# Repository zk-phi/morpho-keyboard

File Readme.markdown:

# Morpho keyboard

スイッチの差し込み位置をずらすことで、一台で色々な Row-staggered 配列を試すことができる分割キーボードです。

スイッチソケットが互い違いに 0.5u 間隔で配置されており、その範囲で好きな位置にキースイッチを移動することができます。

キー数自体も多めになっており、キーマップも含め自分好みのレイアウトを模索することができます。

## 注意

コスト削減のためにプレートの用意がないため、基板のマウント穴とソケットだけでスイッチを支える構造になっています。使い込むうちに、だんだんスイッチの固定がゆるくなってくる可能性が高いです。

打鍵感にこだわった長く使えるキーボード、というよりは自分に合ったキー配列を模索するための実験基板と考えてください。

参考までに、実際に色々な配列を試しながら仕事で使っている私のキーボードは、キーキャップを交換しようとすると一緒にスイッチも外れるようになってきました。普通にタイプする上では今のところ支障ないです。

## 対応しているレイアウト
### アルファベット部分

中段 (ASDF...) を基準に、上段 (QWER...) と下段 (ZXCV...) をそれぞれ左または右に 0.25u ずらすことができます (計 4 通り)。

左右で独立してレイアウトを選べるので、合計 16 通りになります。

代表的なものでは、

- equal row-staggered (HHKB Pro JP など)
- symmetric row-staggered (uTRON keyboard など)
- X row-staggered (Treadstone シリーズ)
- 逆 symmetric row-staggered (Answer40 風)
- 逆 X row-staggered (多分例なし、けど好き)

などを再現できます。

### 親指部分

最大３キー分のスペースがあり、ここに２〜３キー載せることを想定しています。

アルファベット部分が一律 0.5u 間隔になっているのに対して、親指部分は 0.25u ズレと 0.75u ズレを交互に繰り返すようになっています。キーを置きたくなりそうなエリアにソケットを多めに設置して、 0.25u 単位で微調整することを狙っています。

1.25u, 1.75u などの長めのキーキャップを使用することでさらに細かく調整することもできます。

## パーツ

- 基板４枚 (うち２枚は底板として使用)
- いつもの
  - ダイオード 1N4148w 54 個
  - TRRS ジャック MJ-4PP-9 x2
  - 2 ピンタクトスイッチ x2
  - コンスルー付き ProMicro x2 セット
- スイッチ
  - 5pin の MX スイッチ 最大 50 個 (うち 16 個を半田づけ、残りはホットスワップ)
  - MX スイッチソケット 68 個
- ネジ類
  - M2 スペーサ 5mm 10 個
  - M2 ネジ 3~4mm 20 個
  - ゴム足 10 個

## 組み立て

- 基板 4 枚をすべて表 (スイッチの載る四角が並んでいる方) 向きに置きます
  - ４枚それぞれに目印をつけておくと安全です：左手底板、左手基板、右手底板、右手基板
- 左手基板・底板は左の、右手基板・底板は右の親指クラスタが不要なので切り取ります
  - ニッパやカッターで傷つけてからそっと折り取るのがおすすめです、力任せにやると稀に壊れます
  - 一応、切り取らずに６つスイッチを並べてもちゃんと動くと思います (未検証)
- 左右基板にダイオード、スイッチソケットを実装します
  - ダイオードはコの字の目印がカソード
  - *一部のダイオードは向きが逆なので注意*
- 左右基板に TRRS ジャック、タクトスイッチ、キースイッチをこの順に実装します
  - 背の低い部品からつけるのが楽
- コンスルー付き Pro Micro を取り付けてファームウェアを焼きます
  - `zk-phi/qmk_firmware` にあります: `make morpho:phi:avrdude`
- 底板をねじ止めしてゴム足を貼れば完成
  - 底板と基板の向きを揃えないとコンスルーの足が引っかかります

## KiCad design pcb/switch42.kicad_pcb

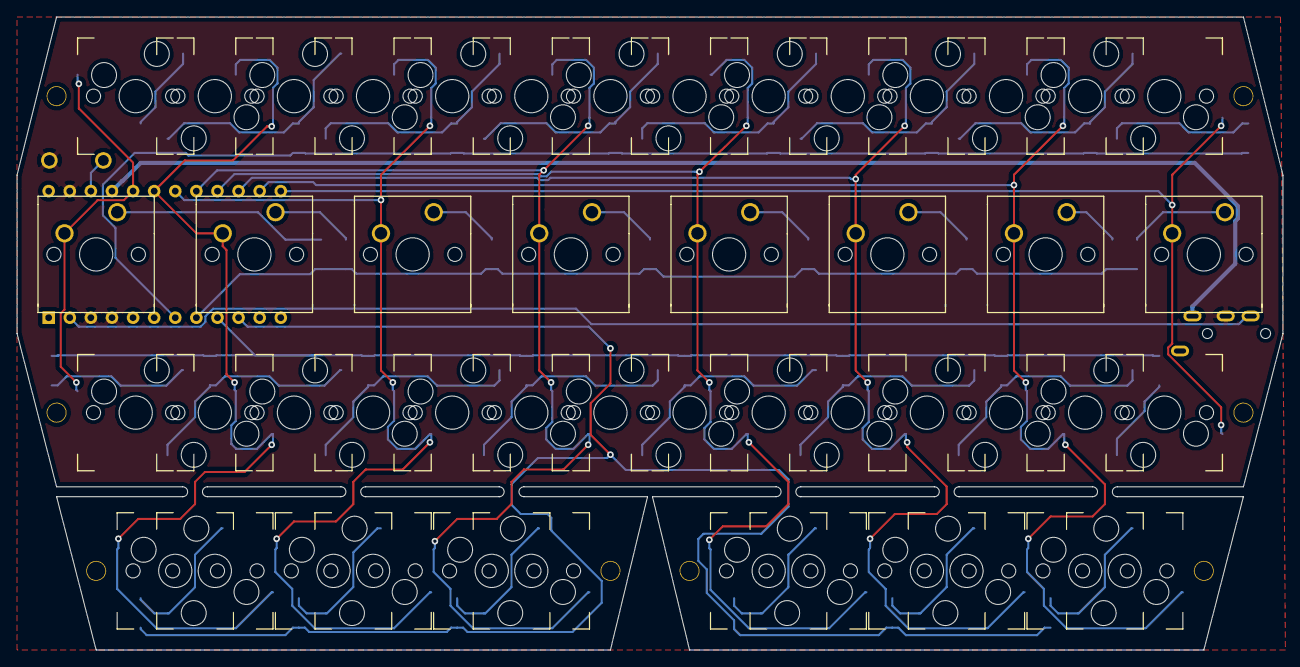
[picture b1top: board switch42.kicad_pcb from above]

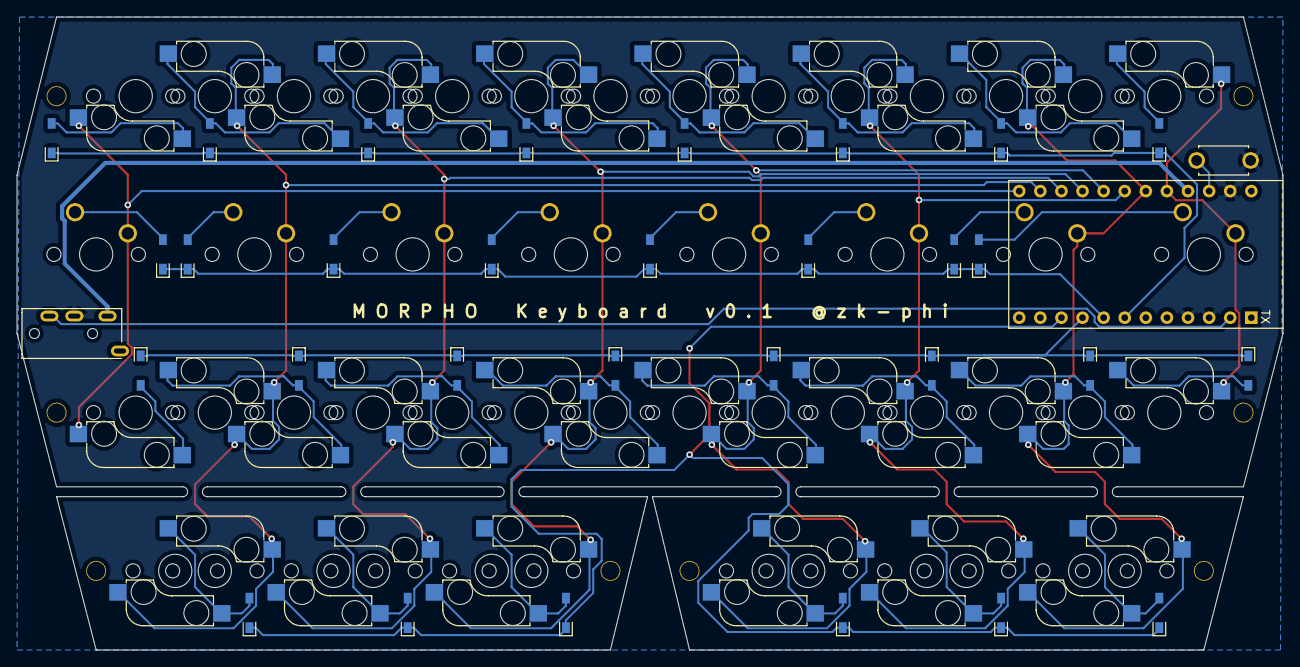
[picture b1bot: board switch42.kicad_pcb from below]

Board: 2 copper layers, 152.4 x 76.2 mm, 89 parts (3 on the bottom side), 46 nets.

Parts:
D1, D2, D3, D4, D5, D6, D7, D8, D9, D10, D11, D12, D13, D14, D15, D16, D17, D18, D19, D20, D21, D22, D23, D24, D25, D26, D27, D28, D29, D30: D; D_SMD-irreversible
J1: MJ-4PP-9; MJ-4PP-9-irreversible
Ref**: Val**; M2_SCREW_HOLE
Ref**#2, Ref**#3, Ref**#4, Ref**#5, Ref**#6, Ref**#7, Ref**#8: Val**; M2_SCREW_HOLE
SW1: SW_PUSH; ResetSW-irreversible
SW2, SW3, SW5, SW6, SW7, SW8, SW9, SW10, SW12, SW13, SW14, SW15, SW16, SW17, SW19, SW20, SW21, SW22, SW24, SW25, SW26, SW27, SW29, SW30, SW31, SW32, SW33, SW34, SW36, SW37, SW38, SW39, SW40, SW41, SW43, SW44, SW46, SW47, SW48, SW49: SW_PUSH; _MX_Hotswap-1.00u-irreversible-smaller-pad
SW4, SW11, SW18, SW23, SW28, SW35, SW42, SW45: SW_PUSH; MX_1.00u-irreversible
U1: ProMicro; ProMicro_Reversed_Conthrough-irreversible

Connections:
GND: J1.C, SW1.2, U1.3, U1.4, U1.23
unnamed: D1.2, SW2.2, SW3.2
unnamed: D2.2, SW4.2
unnamed: D3.2, SW5.2, SW6.2
unnamed: D4.2, SW7.2, SW8.2
unnamed: D5.2, SW9.2, SW10.2
unnamed: D6.2, SW11.2
unnamed: D7.2, SW12.2, SW13.2
unnamed: D8.2, SW14.2, SW15.2
unnamed: D9.2, SW16.2, SW17.2
unnamed: D10.2, SW18.2
unnamed: D11.2, SW19.2, SW20.2
unnamed: D12.2, SW21.2, SW22.2
unnamed: D13.2, SW23.2
unnamed: D14.2, SW24.2, SW25.2
unnamed: D15.2, SW26.2, SW27.2
unnamed: D16.2, SW28.2
unnamed: D17.2, SW29.2, SW30.2
unnamed: D18.2, SW31.2, SW32.2
unnamed: D19.2, SW33.2, SW34.2
unnamed: D20.2, SW35.2
unnamed: D21.2, SW36.2, SW37.2
unnamed: D22.2, SW38.2, SW39.2
unnamed: D23.2, SW41.2
unnamed: D24.2, SW43.2
unnamed: D25.2, SW40.2
unnamed: D26.2, SW42.2
unnamed: D27.2, SW44.2
unnamed: D28.2, SW45.2
unnamed: D29.2, SW46.2, SW47.2
unnamed: D30.2, SW48.2, SW49.2
VCC: J1.D, U1.21
col0: SW40.1, SW42.1, SW44.1, U1.20
col1: SW2.1, SW3.1, SW4.1, SW5.1, SW6.1, SW7.1, SW8.1, U1.19
col2: SW9.1, SW10.1, SW11.1, SW12.1, SW13.1, SW14.1, SW15.1, U1.18
col3: SW16.1, SW17.1, SW18.1, SW19.1, SW20.1, SW46.1, SW47.1, U1.17
col4: SW21.1, SW22.1, SW23.1, SW24.1, SW25.1, SW48.1, SW49.1, U1.16
col5: SW26.1, SW27.1, SW28.1, SW29.1, SW30.1, SW31.1, SW32.1, U1.15
col6: SW33.1, SW34.1, SW35.1, SW36.1, SW37.1, SW38.1, SW39.1, U1.14
col7: SW41.1, SW43.1, SW45.1, U1.13
data: J1.B, U1.2
reset: SW1.1, U1.22
row0: D1.1, D5.1, D9.1, D12.1, D15.1, D19.1, D23.1, D25.1, U1.7
row1: D2.1, D6.1, D10.1, D13.1, D16.1, D20.1, D26.1, D28.1, U1.8
row2: D3.1, D7.1, D11.1, D14.1, D17.1, D21.1, D24.1, D27.1, U1.9
row3: D4.1, D8.1, D18.1, D22.1, D29.1, D30.1, U1.10

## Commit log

2020-01-21 Add Readme
2020-06-12 Add Image
